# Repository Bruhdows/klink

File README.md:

# Klink

Klink is an 80x80mm magnetic tile system for programmable marble runs. V1 keeps sixteen identical intelligent tiles, a six-port Hub, removable modules and a motorized elevator for continuous circulation. Sensors, buttons, RGB LEDs and a gate let a program react to marbles and people.

The design is in progress. It is not ready for main-board fabrication or Fallen Design Submission. The remaining digital work and physical qualification gates are listed below.

TODO: Add the participant's own explanation of why they are making Klink. Personal design narrative, journals and demonstrations must describe their actual work.

## Operation

A USB-C PD supply feeds a 20V bus through the Hub's independent protection and common shutdown. Each tile makes local 5V and 3.3V, has four independent UART links, two RGB LEDs and protected module supplies. Local 5V rails never connect between tiles. The Hub's input cutoff is approximately 4.2A nominal; accepting a 100W adapter does not guarantee 100W delivered to tiles.

Buildable firmware provides discovery, hardware-UID identification, address assignment, topology reporting, framed/CRC-protected routing, module identification, power leases, RGB/PWM/I2C access and fault handling. The Hub stores a small event program and its tile bindings for standalone operation. A POSIX USB commissioning client is included. The elevator controller has default-off motor control, progress/current monitoring, a normally closed stop and latched fault recovery. None of these images has run on assembled Klink hardware.

After hardware qualification, commission known modules and upload rules over the separate USB data port. The stored program can run without a permanently connected computer. Protocol capacity targets 64 tiles; permissible power depends on topology and admitted loads. Disconnect bus power before rearranging tiles.

## Design views

[FreeCAD assembly source](hardware/cad/assembly.FCStd) includes the electronics, lift, return, gate, support rods and baseboard. Some component models, input-module cases, connectors and harnesses remain incomplete. This is a CAD reference, not a photograph or a full collision qualification.

Tile placement and partial routing. The MCU and several custom parts have missing 3D models. [Copper plot](docs/images/tile.svg).

Hub placement and partial routing. All 350 schematic circuit references are represented on the PCB; routing remains incomplete. [Copper plot](docs/images/hub.svg).

The elevator layout is fully connected and passes native DRC. Electrical/thermal bring-up remains necessary.

## Files

- [Editable KiCad projects and board BOMs](hardware/electronics/).
- [CAD sources, individual STEP/STL exports and assembly notes](hardware/cad/README.md).
- [Manufacturing drafts, Gerber ZIPs, drills, BOM/CPL and validation summary](hardware/manufacturing/README.md).
- [Firmware source, offline build instructions, tests and USB client](firmware/README.md).
- [Consolidated purchase/funding BOM](bom.csv) and [cost basis](docs/specifications/BOM.md).
- [Electrical design](docs/specifications/rev-a.md), [interfaces and orientation](docs/specifications/interfaces.md), and [prototype tests](docs/specifications/prototype-plan.md).

## Validation and funding

Native KiCad 10.0.8 ERC passes on all six circuit schematics. Elevator, button, sensor and gate have zero physical DRC violations, unconnected items or schematic-parity errors. Tile and Hub have zero physical DRC violations, but still have 63 and 317 unconnected items respectively. Tile J3-J7 have no released footprints. Those boards have no fabrication package. The [summary](hardware/manufacturing/validation.json) records source hashes and the incomplete state.

All three MCU targets compile. Host C protocol/safety tests pass with address and undefined-behavior sanitizers, alongside the Python client tests. Closed individual print meshes and STEP exports have been checked; physical fit, loads, temperature, signal integrity and protection transients remain untested.

The complete sixteen-tile worksheet is approximately USD 1,372.89 plus a separately identified USD 343.22 uncertainty allowance, or USD 1,716.11. This is not a verified supplier quote or approved grant amount. Many parts/services still use clearly marked allowances, and some material rows still need exact purchase SKUs/links. TPS26630 remains a backorder item; the newer TPS259470 listing shows sufficient stock, but live stock and assembly inventory need confirmation. The cost basis records a USD 71.20 reduction in the base estimate, including listed Polish N45 magnets and domestic delivery; most rows remain unquoted. The 3/5-tile trial estimates are separate and should not be added to the sixteen-tile total. Owned PETG and tools are not charged again.

## Before submission and manufacturing

Finish the remaining tile/Hub routing, power/return and USB layout review, missing models and fabrication checks. Qualify edge/top contacts and their fault transients before releasing connector geometry. Complete the module cases, optical mounts, harnesses and interactive marble route against that interface. Obtain delivered parts/assembly quotes and replace provisional material links and allowances.

This revision includes AI assistance with firmware, engineering edits, checks and exports. The participant must add their own original design explanation and genuine journals, review the design and publish the reviewed revision. Approval and funding eligibility are not established by the files in this repository. After funding, follow the current-limited contact/protection, PCB bring-up, print-fit, sensor, gate, motor and continuous-run tests in the prototype plan. No build photographs or successful hardware tests are claimed.

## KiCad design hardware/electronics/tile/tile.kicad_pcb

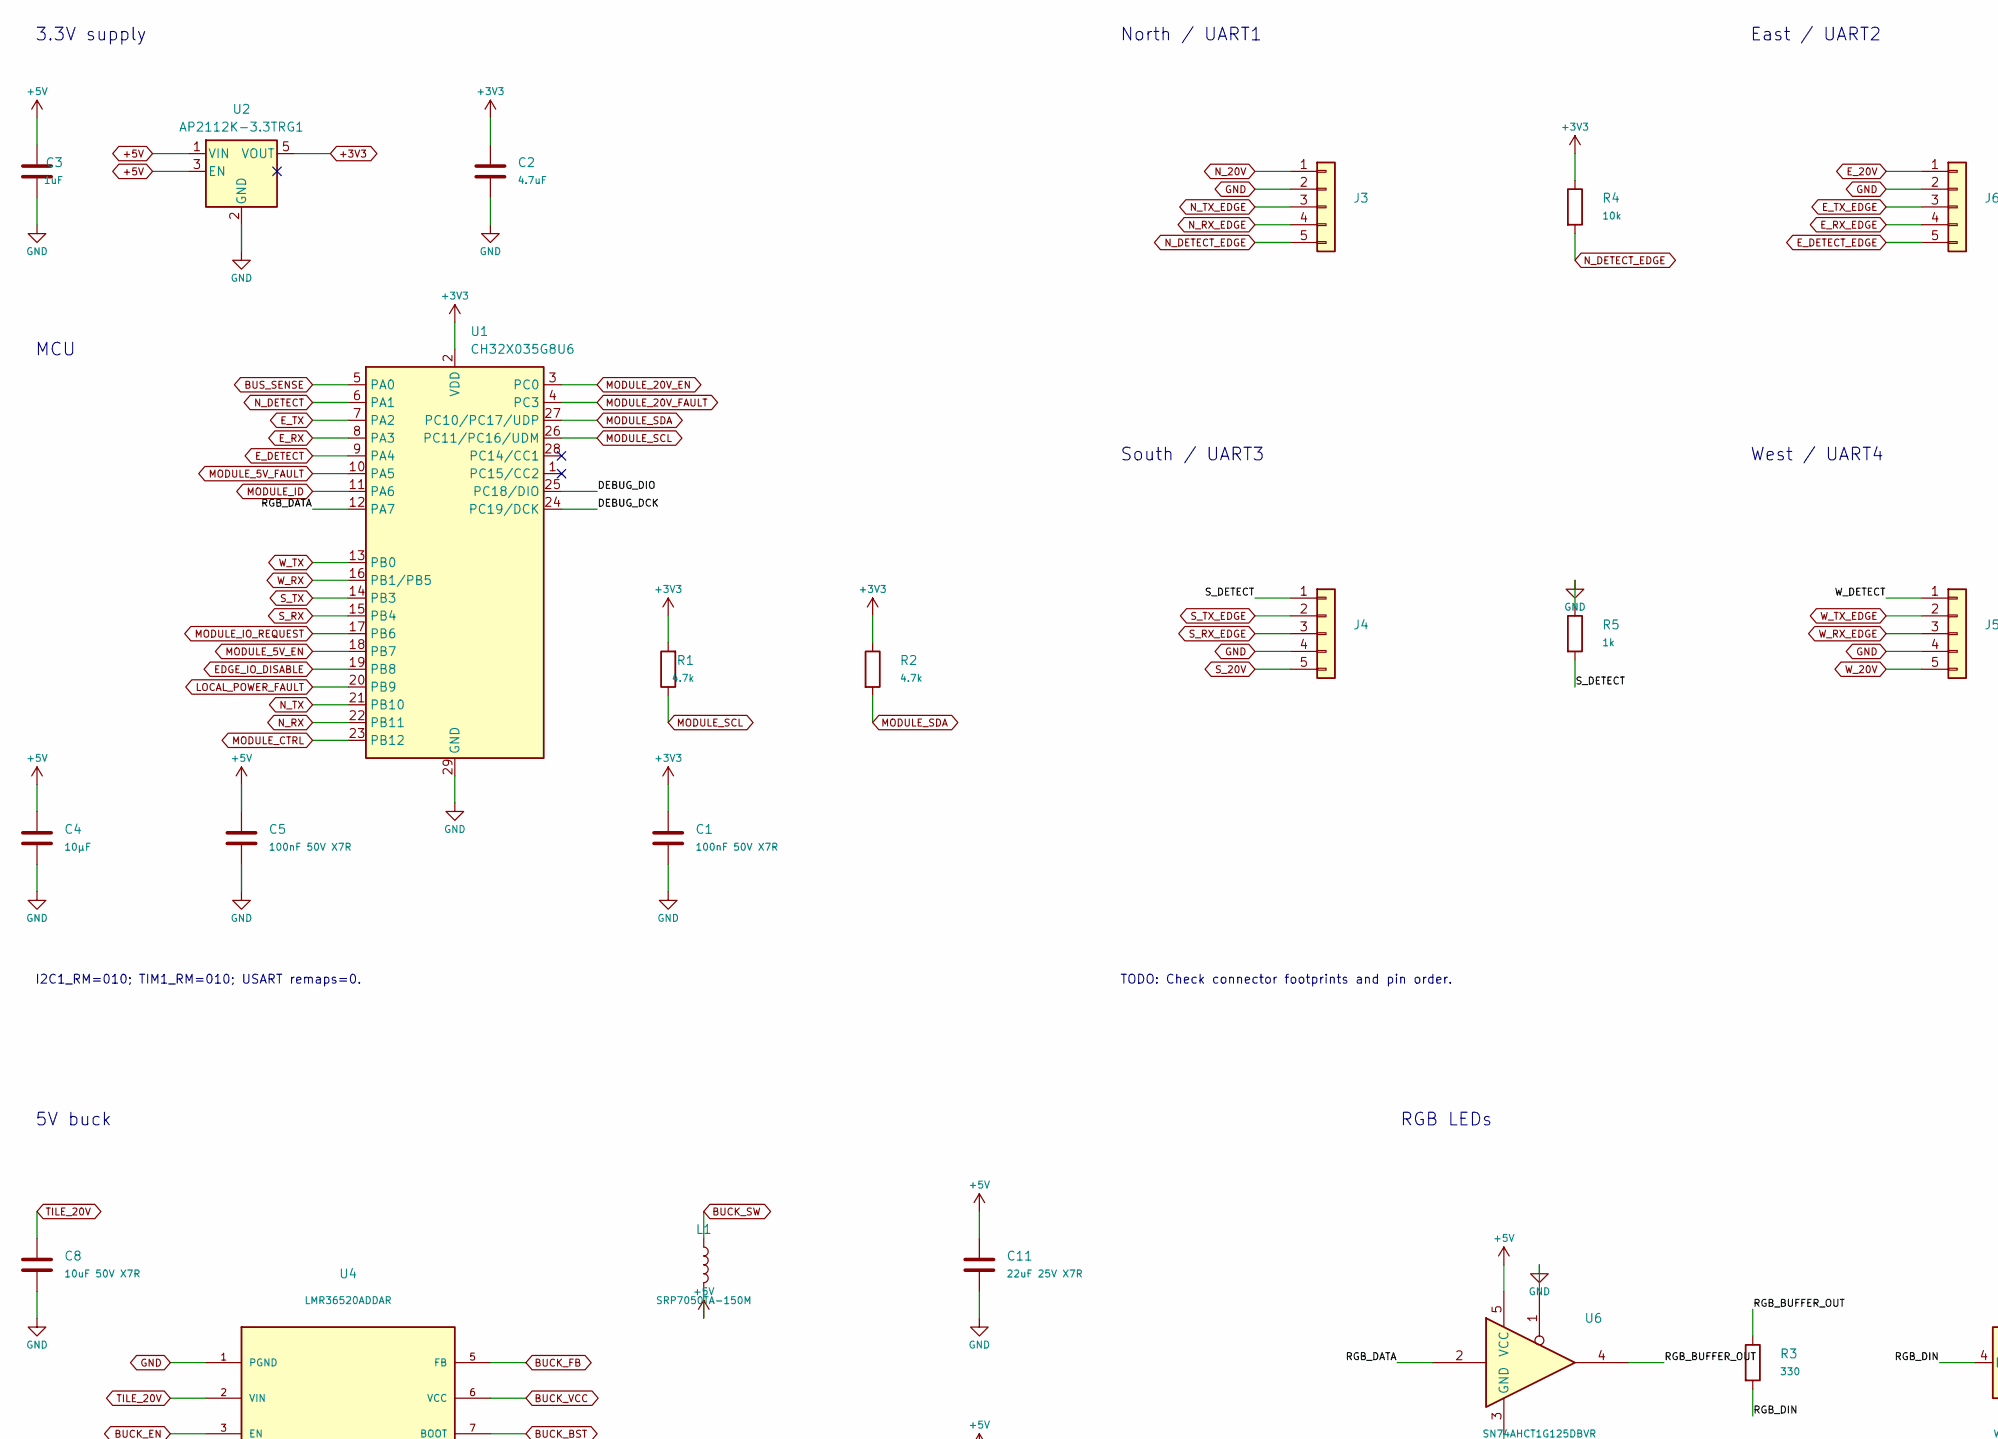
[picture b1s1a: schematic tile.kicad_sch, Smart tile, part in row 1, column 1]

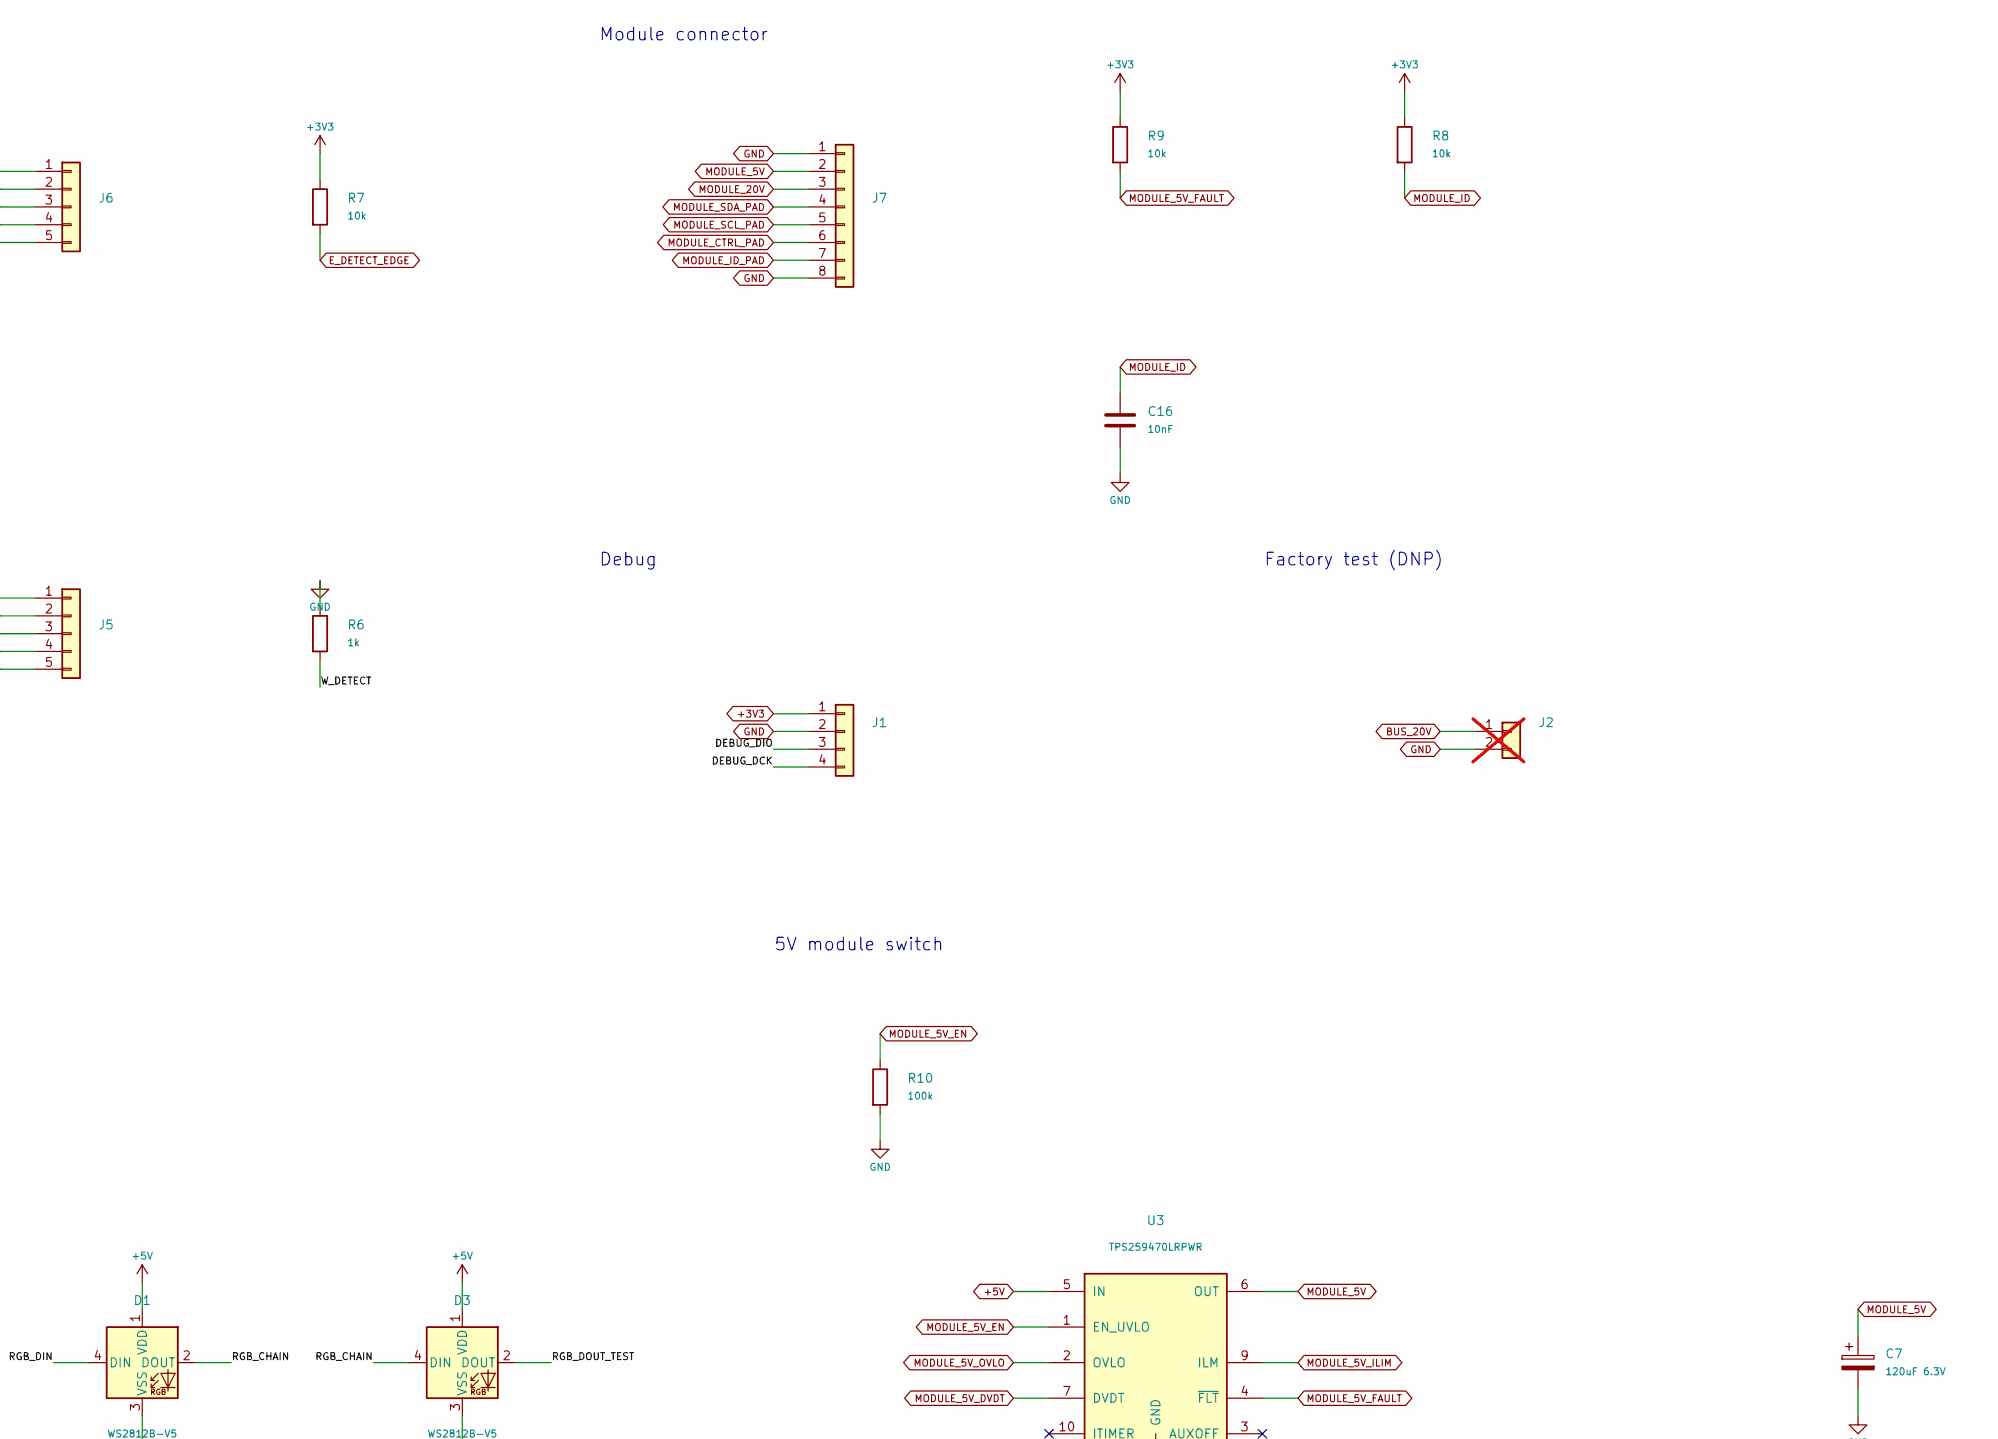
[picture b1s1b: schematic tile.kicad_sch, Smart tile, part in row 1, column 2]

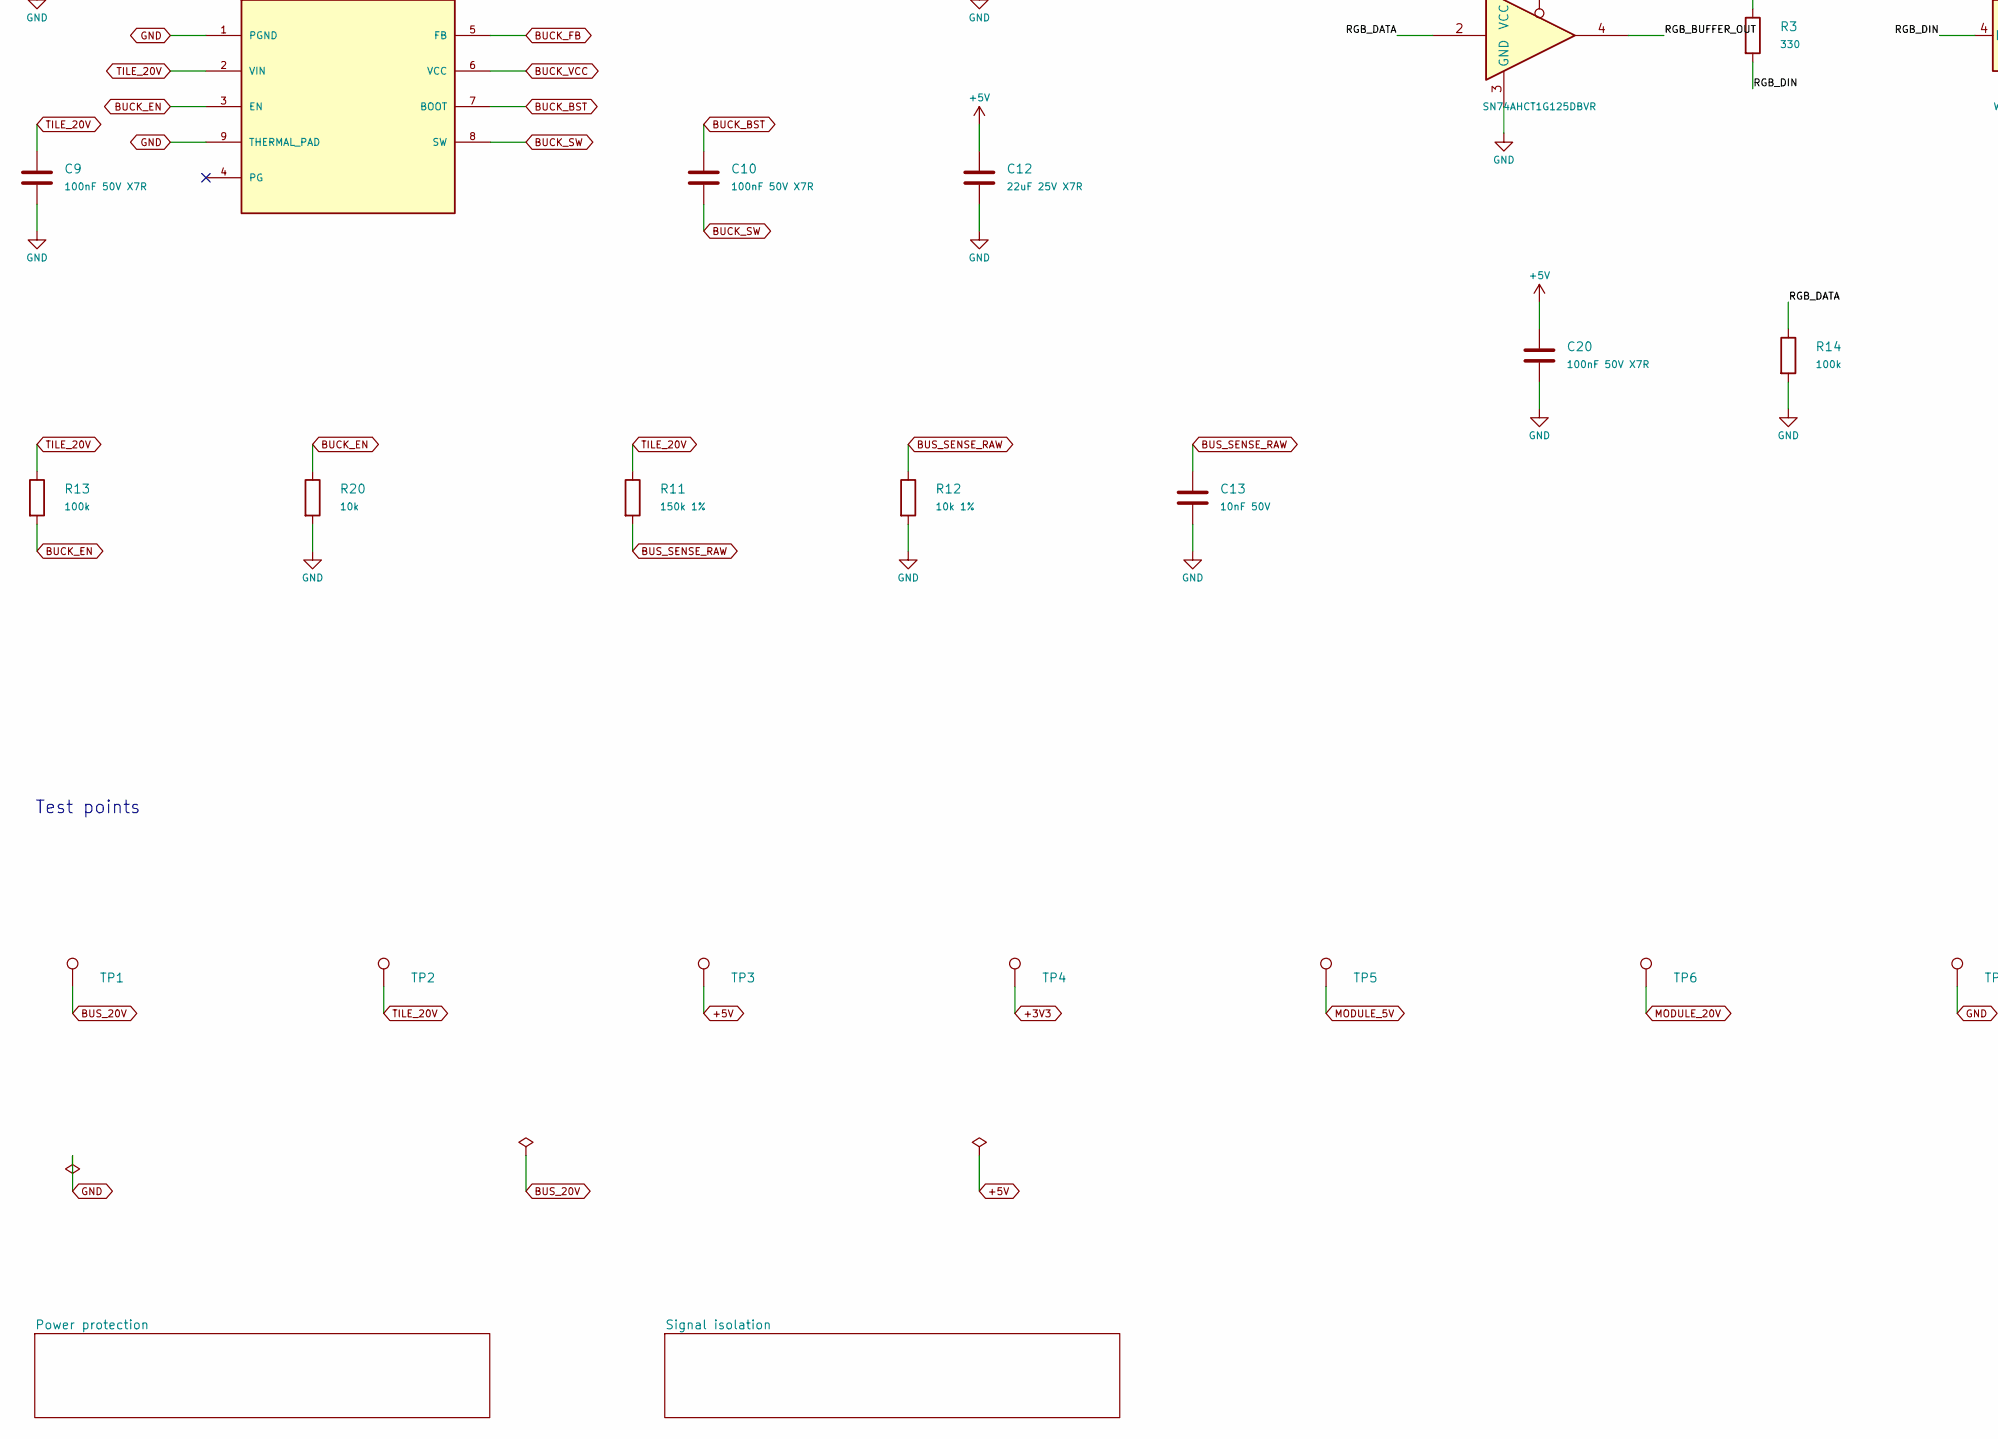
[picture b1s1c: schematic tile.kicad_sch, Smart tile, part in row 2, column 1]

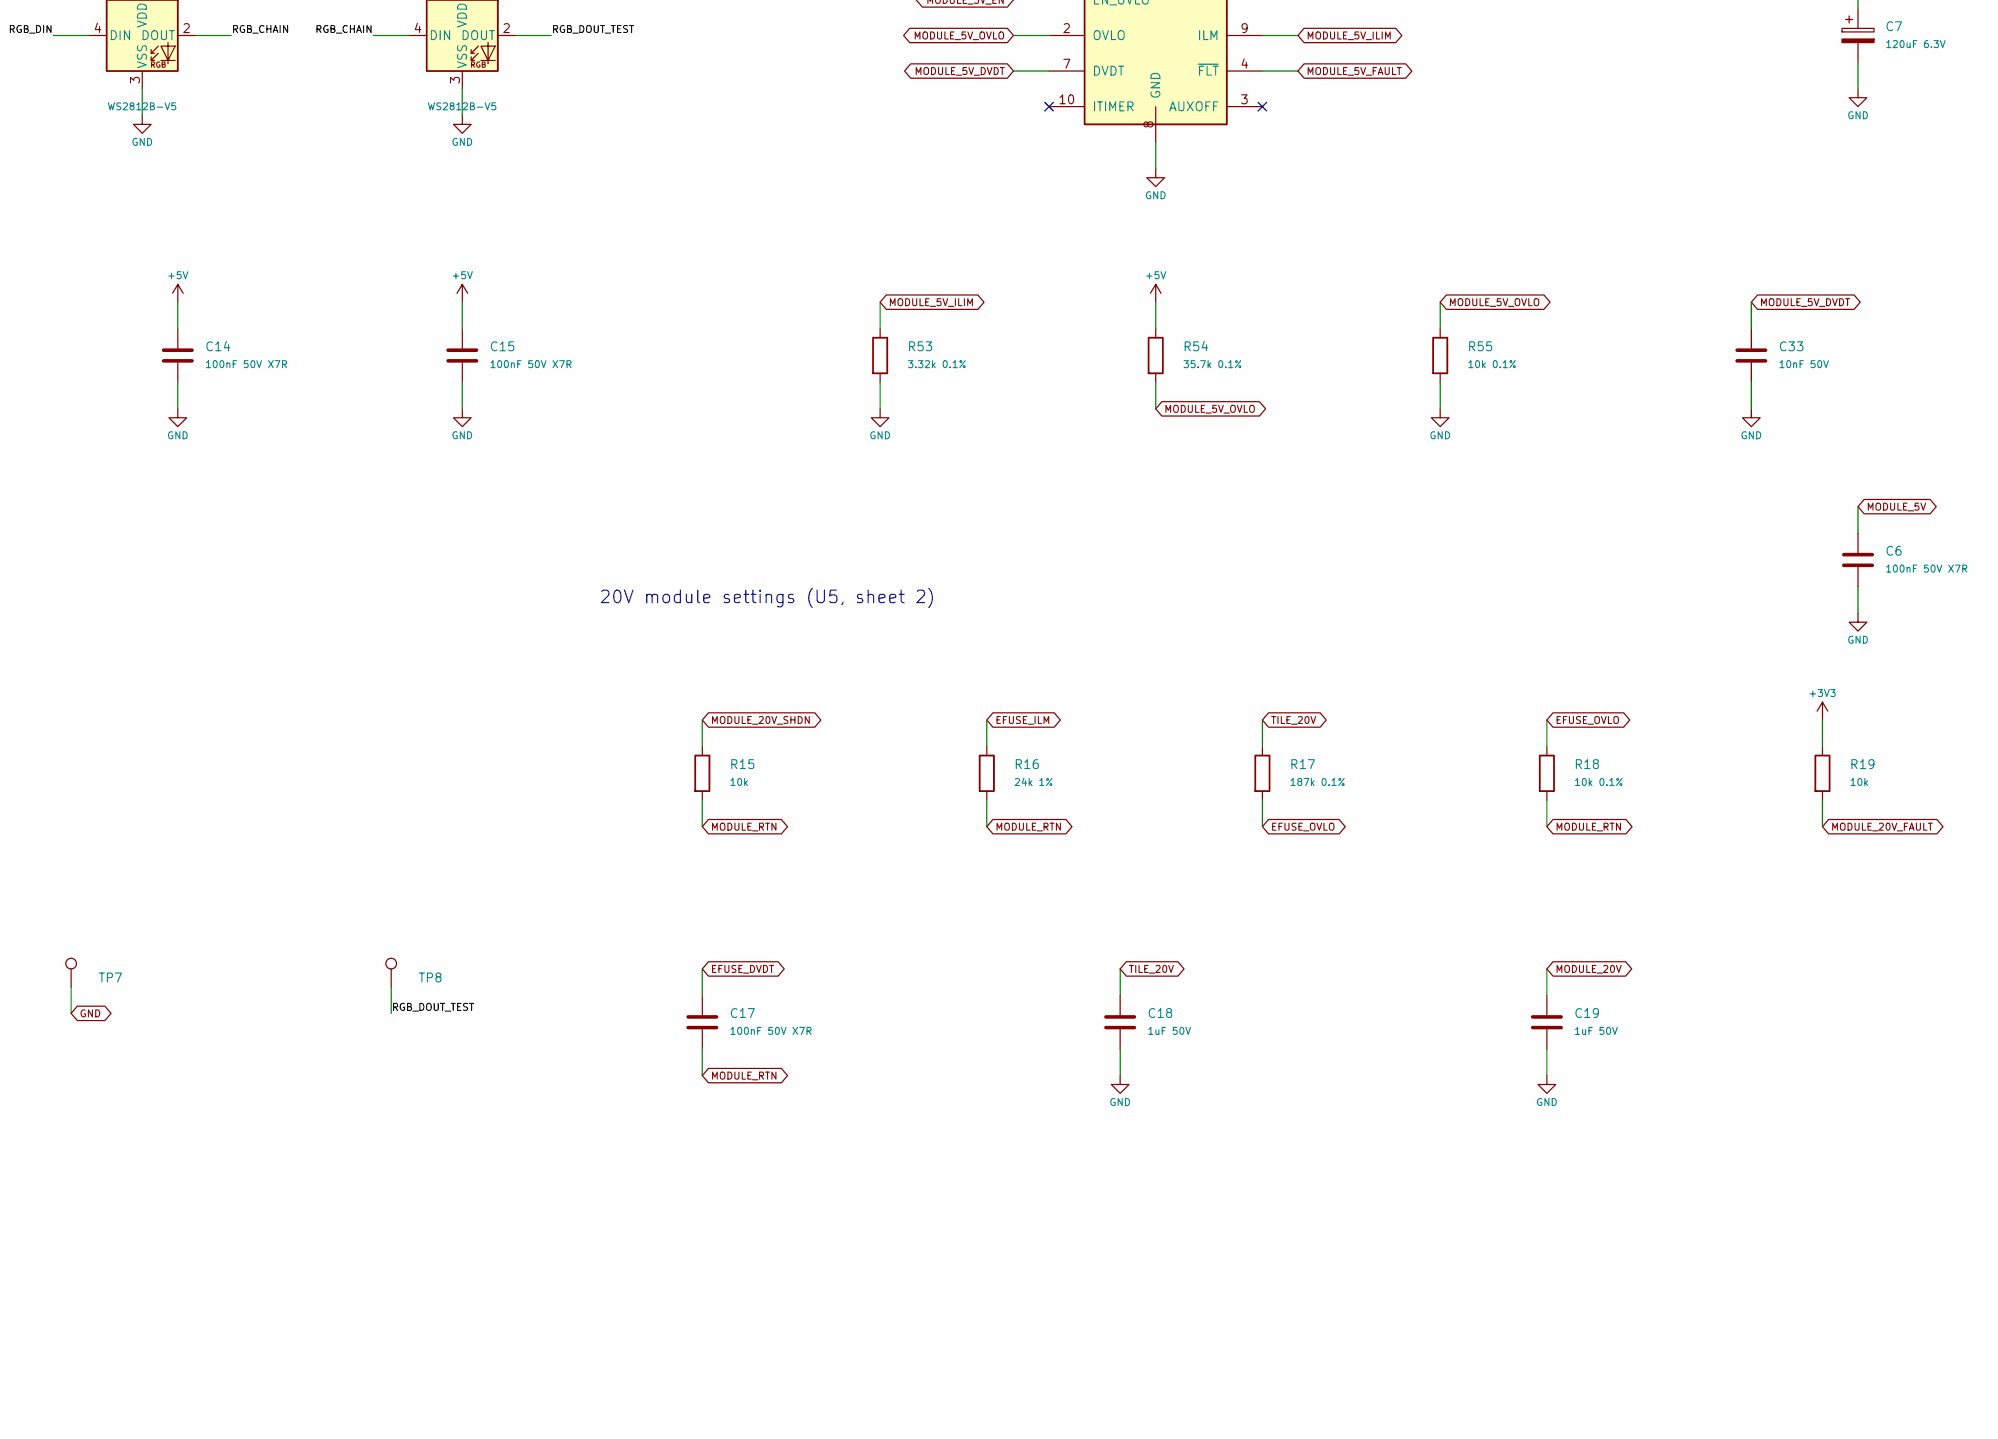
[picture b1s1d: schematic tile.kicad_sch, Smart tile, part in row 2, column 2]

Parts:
C1, C5, C6, C9, C10, C14, C15, C17, C20: 100nF 50V X7R; C_0805_2012Metric; MPN C2012X7R1H104K125AE
C2: 4.7uF; C_0805_2012Metric; MPN C2012X7R1C475K125AB
C3: 1uF; C_0805_2012Metric; MPN C2012X7R1H105K125AB
C4: 10µF; C_1206_3216Metric; MPN C3216X7R1C106K160AC
C7: 120uF 6.3V; CP_Panasonic_POSCAP_B2; ManufacturerPartNumber 6TPE120MAZB
C8: 10uF 50V X7R; C_1206_3216Metric; MPN C3216X7R1H106K160AC
C11, C12: 22uF 25V X7R; C_1210_3225Metric; MPN C1210C226K3RACTU
C13, C33: 10nF 50V; C_0805_2012Metric; MPN CC0805KRX7R9BB103
C16: 10nF; C_0805_2012Metric; MPN CC0805KRX7R9BB103
C18, C19: 1uF 50V; C_0805_2012Metric; MPN C2012X7R1H105K125AB
D1, D3: WS2812B-V5; LED_WS2812B_PLCC4_5.0x5.0mm_P3.2mm
J1: DEBUG_3V3_MONITOR; Debug_1x04_P2.54_Pads
J2: DNP_FACTORY_BUS_TEST; not fitted
J3, J4, J5, J6: EDGE_5P_TBD
J7: Conn_01x08
L1: SRP7050TA-150M; L_Bourns_SRP7050TA
R1, R2: 4.7k; R_0805_2012Metric; MPN RC0805FR-074K7L
R3: 330; R_0805_2012Metric; MPN RC0805FR-07330RL
R4, R7, R8, R9, R15, R19, R20: 10k; R_0805_2012Metric; MPN RC0805FR-0710KL
R5, R6: 1k; R_0805_2012Metric; MPN RC0805FR-071KL
R10, R13, R14: 100k; R_0805_2012Metric; MPN RC0805FR-07100KL
R11: 150k 1%; R_0805_2012Metric; MPN RC0805FR-07150KL
R12: 10k 1%; R_0805_2012Metric; MPN RC0805FR-0710KL
R16: 24k 1%; R_0805_2012Metric; MPN RC0805FR-0724KL
R17: 187k 0.1%; R_0805_2012Metric; MPN RT0805BRD07187KL
R18, R55: 10k 0.1%; R_0805_2012Metric; MPN RT0805BRD0710KL
R53: 3.32k 0.1%; R_0805_2012Metric; MPN RT0805BRD073K32L
R54: 35.7k 0.1%; R_0805_2012Metric; MPN RT0805BRD0735K7L
TP1: BUS_20V; TestPoint_Pad_D2.0mm
TP2: TILE_20V; TestPoint_Pad_D2.0mm
TP3: +5V; TestPoint_Pad_D2.0mm
TP4: +3V3; TestPoint_Pad_D2.0mm
TP5: MODULE_5V; TestPoint_Pad_D2.0mm
TP6: MODULE_20V; TestPoint_Pad_D2.0mm
TP7: GND; TestPoint_Pad_D2.0mm
TP8: RGB_DOUT_TEST; TestPoint_Pad_D2.0mm
U1: CH32X035G8U6; WQFN-28-1EP_4x4mm_P0.4mm_EP2.7x2.7mm
U2: AP2112K-3.3TRG1; SOT-23-5
U3: TPS259470LRPWR; TI_RPW0010A_2x2mm
U4: LMR36520ADDAR; TI_SO-PowerPAD-8
U6: SN74AHCT1G125DBVR; SOT-23-5

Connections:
+3V3: C1.1, C2.1, J1.1, R1.2, R2.1, R4.1, R7.1, R8.1, R9.1, R19.1, TP4.1, U1.2 (VDD), U2.5 (VOUT); also elsewhere on the board
+5V: C3.2, C4.1, C5.1, C11.1, C12.1, C14.1, C15.1, C20.1, D1.1 (VDD), D3.1 (VDD), L1.2, R54.1, TP3.1, U2.1 (VIN), U2.3 (EN), U3.5 (IN), U6.5 (VCC); also elsewhere on the board
/DEBUG_DCK: J1.4, U1.24 (PC19/DCK)
/DEBUG_DIO: J1.3, U1.25 (PC18/DIO)
/RGB_BUFFER_OUT: R3.1, U6.4
/RGB_CHAIN: D1.2 (DOUT), D3.4 (DIN)
/RGB_DATA: R14.1, U1.12 (PA7), U6.2
/RGB_DIN: D1.4 (DIN), R3.2
/RGB_DOUT_TEST: D3.2 (DOUT), TP8.1
/S_DETECT: J4.1, R5.2
/W_DETECT: J5.1, R6.2
BUCK_BST: C10.1, U4.7 (BOOT)
BUCK_EN: R13.2, R20.1, U4.3 (EN)
BUCK_FB: U4.5 (FB); also elsewhere on the board
BUCK_SW: C10.2, L1.1, U4.8 (SW)
BUCK_VCC: U4.6 (VCC); also elsewhere on the board
BUS_20V: J2.1, TP1.1; also elsewhere on the board
BUS_SENSE: U1.5 (PA0); also elsewhere on the board
BUS_SENSE_RAW: C13.1, R11.2, R12.1; also elsewhere on the board
EDGE_IO_DISABLE: U1.19 (PB8); also elsewhere on the board
EFUSE_DVDT: C17.1; also elsewhere on the board
EFUSE_ILM: R16.1; also elsewhere on the board
EFUSE_OVLO: R17.2, R18.1; also elsewhere on the board
E_DETECT: U1.9 (PA4); also elsewhere on the board
E_DETECT_EDGE: J6.5, R7.2; also elsewhere on the board
E_RX: U1.8 (PA3); also elsewhere on the board
E_TX: U1.7 (PA2); also elsewhere on the board
GND: C1.2, C2.2, C3.1, C4.2, C5.2, C6.2, C7.2, C8.2, C9.2, C11.2, C12.2, C13.2, C14.2, C15.2, C16.2, C18.2, C19.2, C20.2, C33.2, D1.3 (VSS), D3.3 (VSS), J1.2, J2.2, J3.2, J4.4, J5.4, J6.2, J7.1, J7.8, R5.1, R6.1, R10.2, R12.2, R14.2, R20.2, R53.2, R55.2, TP7.1, U1.29 (GND), U2.2 (GND), U3.8 (GND), U4.1 (PGND), U4.9 (THERMAL_PAD), U6.1, U6.3 (GND); also elsewhere on the board
LOCAL_POWER_FAULT: U1.20 (PB9); also elsewhere on the board
MODULE_5V: C6.1, C7.1, J7.2, TP5.1, U3.6 (OUT); also elsewhere on the board
MODULE_5V_DVDT: C33.1, U3.7 (DVDT)
MODULE_5V_EN: R10.1, U1.18 (PB7), U3.1 (EN_UVLO)
MODULE_5V_FAULT: R9.2, U1.10 (PA5), U3.4 (~FLT)
MODULE_5V_ILIM: R53.1, U3.9 (ILM)
MODULE_5V_OVLO: R54.2, R55.1, U3.2 (OVLO)
MODULE_20V: C19.1, J7.3, TP6.1; also elsewhere on the board
MODULE_20V_EN: U1.3 (PC0); also elsewhere on the board
MODULE_20V_FAULT: R19.2, U1.4 (PC3); also elsewhere on the board
MODULE_20V_SHDN: R15.1; also elsewhere on the board
MODULE_CTRL: U1.23 (PB12); also elsewhere on the board
MODULE_ID: C16.1, R8.2, U1.11 (PA6); also elsewhere on the board
MODULE_IO_REQUEST: U1.17 (PB6); also elsewhere on the board
MODULE_RTN: C17.2, R15.2, R16.2, R18.2; also elsewhere on the board
MODULE_SCL: R1.1, U1.26 (PC11/PC16/UDM); also elsewhere on the board
MODULE_SDA: R2.2, U1.27 (PC10/PC17/UDP); also elsewhere on the board
N_DETECT: U1.6 (PA1); also elsewhere on the board
N_DETECT_EDGE: J3.5, R4.2; also elsewhere on the board
N_RX: U1.22 (PB11); also elsewhere on the board
N_TX: U1.21 (PB10); also elsewhere on the board
S_RX: U1.15 (PB4); also elsewhere on the board
S_TX: U1.14 (PB3); also elsewhere on the board
TILE_20V: C8.1, C9.1, C18.1, R11.1, R13.1, R17.1, TP2.1, U4.2 (VIN); also elsewhere on the board
W_RX: U1.16 (PB1/PB5); also elsewhere on the board
W_TX: U1.13 (PB0); also elsewhere on the board

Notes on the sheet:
3.3V supply
MCU
North / UART1
East / UART2
South / UART3
West / UART4
Module connector
Debug
Factory test (DNP)
5V buck
RGB LEDs
5V module switch
20V module settings (U5, sheet 2)
Test points
I2C1_RM=010; TIM1_RM=010; USART remaps=0.
TODO: Check connector footprints and pin order.
